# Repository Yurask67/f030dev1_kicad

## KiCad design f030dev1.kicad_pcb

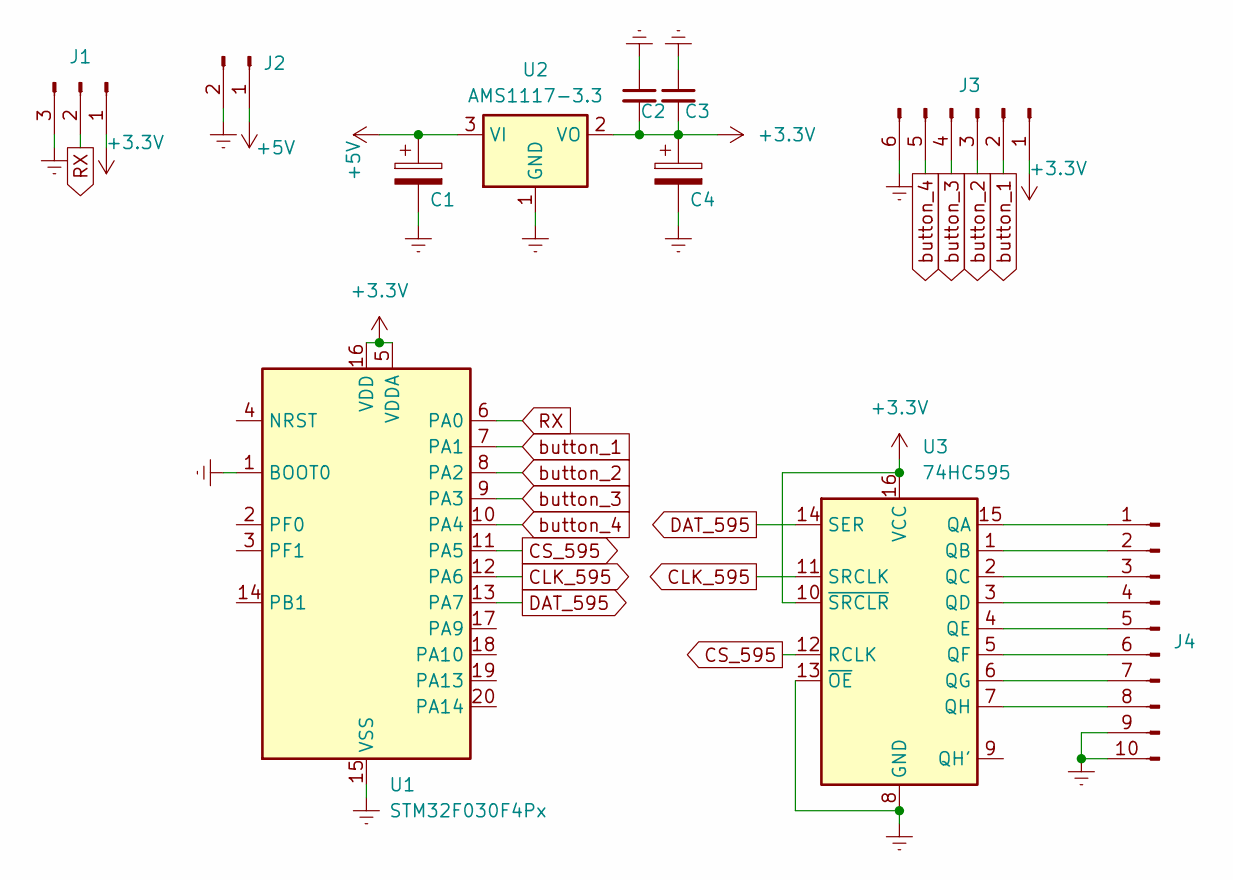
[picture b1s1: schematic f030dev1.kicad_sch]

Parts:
C1, C4: C_Polarized; CP_Radial_D7.5mm_P2.50mm
C2, C3: C_Small; C_0805_2012Metric_Pad1.18x1.45mm_HandSolder
J1: Conn_01x03_Pin; PinSocket_1x03_P2.00mm_Vertical
J2: Conn_01x02_Pin; PinHeader_1x02_P2.54mm_Vertical
J3: Conn_01x06_Pin; PinHeader_1x06_P2.54mm_Vertical
J4: Conn_01x10_Pin; PinHeader_2x05_P2.54mm_Vertical
U1: STM32F030F4Px; TSSOP-20_4.4x6.5mm_P0.65mm
U2: AMS1117-3.3; SOT-223-3_TabPin2
U3: 74HC595; DIP-16_W7.62mm_LongPads

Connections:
+3.3V: C2.2, C3.2, C4.1, J1.1, J3.1, U1.5 (VDDA), U1.16 (VDD), U2.2 (VO), U3.10 (~SRCLR), U3.16 (VCC)
+5V: C1.1, J2.1, U2.3 (VI)
CLK_595: U1.12 (PA6), U3.11 (SRCLK)
CS_595: U1.11 (PA5), U3.12 (RCLK)
DAT_595: U1.13 (PA7), U3.14 (SER)
GNDREF: C1.2, C2.1, C3.1, C4.2, J1.3, J2.2, J3.6, J4.9, J4.10, U1.1 (BOOT0), U1.15 (VSS), U2.1 (GND), U3.8 (GND), U3.13 (~OE)
unnamed: J4.1, U3.15 (QA)
unnamed: J4.2, U3.1 (QB)
unnamed: J4.3, U3.2 (QC)
unnamed: J4.4, U3.3 (QD)
unnamed: J4.5, U3.4 (QE)
unnamed: J4.6, U3.5 (QF)
unnamed: J4.7, U3.6 (QG)
unnamed: J4.8, U3.7 (QH)
RX: J1.2, U1.6 (PA0)
button_1: J3.2, U1.7 (PA1)
button_2: J3.3, U1.8 (PA2)
button_3: J3.4, U1.9 (PA3)
button_4: J3.5, U1.10 (PA4)

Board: 2 copper layers, 11 parts (4 on the bottom side), 19 nets, no tracks yet.

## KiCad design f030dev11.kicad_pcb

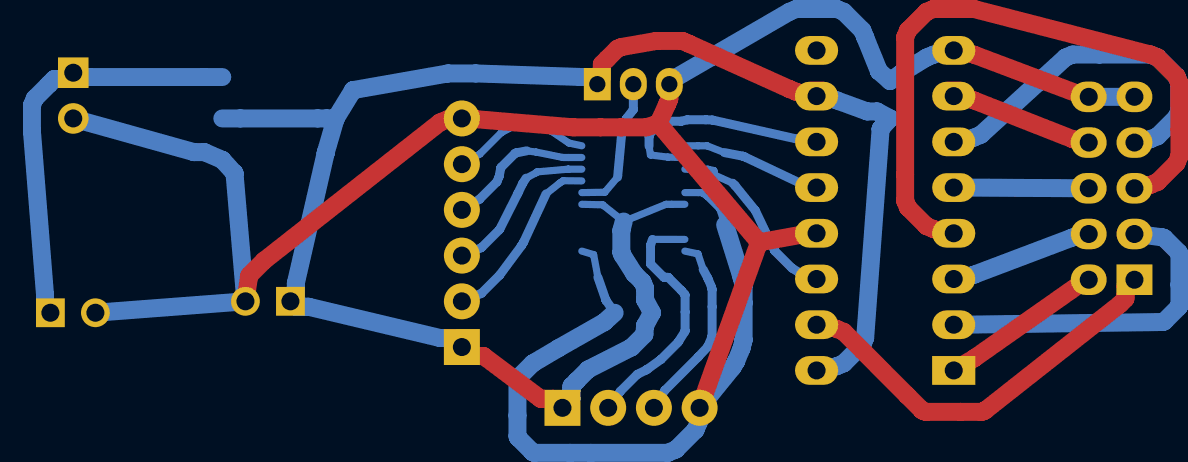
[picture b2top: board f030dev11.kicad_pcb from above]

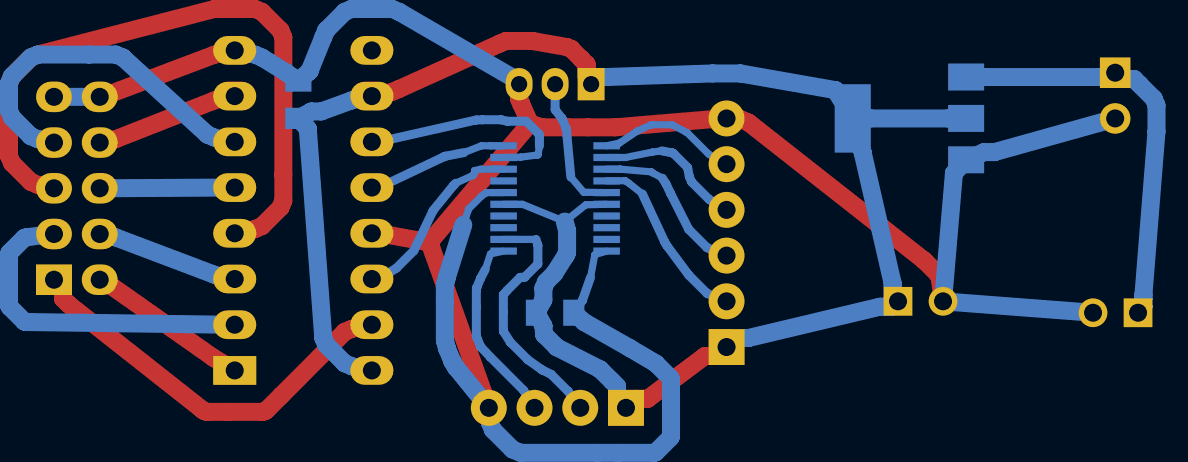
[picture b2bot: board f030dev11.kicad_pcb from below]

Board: 2 copper layers, 12 parts (4 on the bottom side), 21 nets.

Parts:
C1: C1
C2: C2
C3: C3
C4: C4
J1: J1
J2: J2
J3: J3
J4: J4
J5: J5
U1: U1
U2: U2
U3: U3

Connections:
+3.3V: C2.2, C3.2, C4.1, J1.1, J3.1, J4.1, U1.5, U1.16, U2.2, U2.2@1, U3.10, U3.16
+5V: C1.1, J2.1, U2.3
CLK_595: U1.12, U3.11
CS_595: U1.11, U3.12
DAT_595: U1.13, U3.14
GNDREF: C1.2, C2.1, C3.1, C4.2, J1.3, J2.2, J3.4, J4.6, J5.9, J5.10, U1.1, U1.15, U2.1, U3.8, U3.13
unnamed: J3.2, U1.19
unnamed: J3.3, U1.20
unnamed: J5.1, U3.15
unnamed: J5.2, U3.1
unnamed: J5.3, U3.2
unnamed: J5.4, U3.3
unnamed: J5.5, U3.4
unnamed: J5.6, U3.5
unnamed: J5.7, U3.6
unnamed: J5.8, U3.7
RX: J1.2, U1.6
button_1: J4.2, U1.7
button_2: J4.3, U1.8
button_3: J4.4, U1.9
button_4: J4.5, U1.10

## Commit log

2025-02-25 init
2025-02-25 в процесе
2025-02-26 Старт
    схему нужно проверять
2025-02-28 SWDIO add
    добавлен разъем для программирования
2025-03-03 process
